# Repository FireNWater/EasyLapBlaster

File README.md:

# EasyLapBlaster
Quad Racing Airborne IR Transmitter

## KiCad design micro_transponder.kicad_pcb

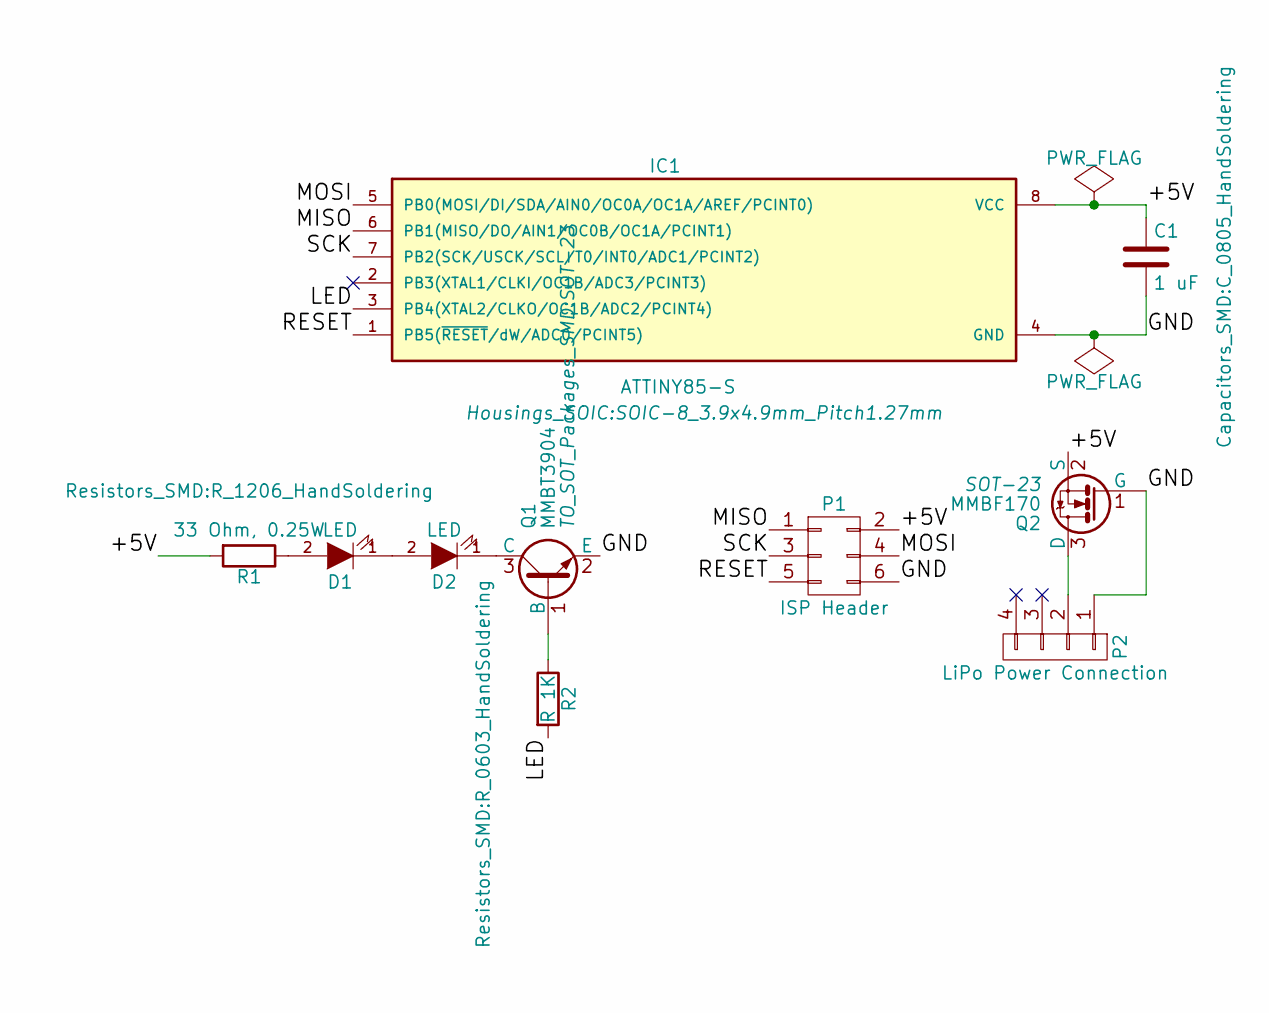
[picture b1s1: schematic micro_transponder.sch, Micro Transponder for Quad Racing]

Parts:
C1: 1 uF; C_0805_HandSoldering
D1, D2: LED; LED-5MM; DigiKey Part 1497-1205-1-ND
IC1: ATTINY85-S; SOIC-8_3.9x4.9mm_Pitch1.27mm
P1: ISP Header; Pin_Header_Straight_2x03
P2: LiPo Power Connection; Pin_Header_Angled_1x04
Q1: MMBT3904; SOT-23
Q2: MMBF170; SOT-23
R1: 33 Ohm, 0.25W; R_1206_HandSoldering; DigiKey Part 541-150SCT-ND
R2: R 1K; R_0603_HandSoldering

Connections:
/+5V: C1.1, IC1.8 (VCC), P1.2, Q2.2 (S), R1.2
/GND: C1.2, IC1.4 (GND), P1.6, P2.1, Q1.2 (E), Q2.1 (G)
/LED: IC1.3 (PB4(XTAL2/CLKO/OC1B/ADC2/PCINT4)), R2.2
/MISO: IC1.6 (PB1(MISO/DO/AIN1/OC0B/OC1A/PCINT1)), P1.1
/MOSI: IC1.5 (PB0(MOSI/DI/SDA/AIN0/OC0A/OC1A/AREF/PCI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), P1.4
/RESET: IC1.1 (PB5(~RESET~/dW/ADC0/PCINT5)), P1.5
/SCK: IC1.7 (PB2(SCK/USCK/SCL/T0/INT0/ADC1/PCINT2)), P1.3
unnamed: D1.1 (K), D2.2 (A)
unnamed: D1.2 (A), R1.1
unnamed: D2.1 (K), Q1.3 (C)
unnamed: P2.2, Q2.3 (D)
unnamed: Q1.1 (B), R2.1

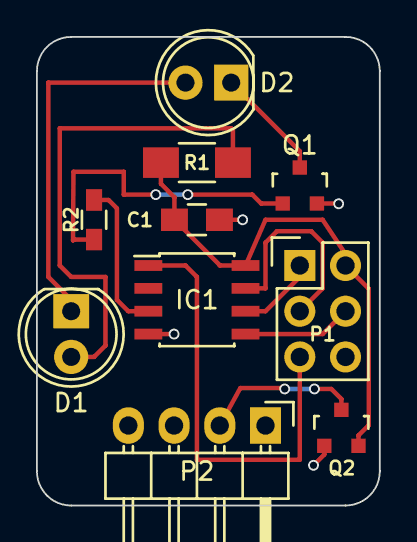
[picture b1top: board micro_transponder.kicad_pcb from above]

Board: 2 copper layers, 19.1 x 26.0 mm, 10 parts (0 on the bottom side), 12 nets.
